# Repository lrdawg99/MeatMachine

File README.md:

# MeatMachine
Internet connected electric meat smoker

BOM
=======
- 1 Thermocouple https://www.sparkfun.com/products/251
- 1 Therm. amp. https://www.adafruit.com/products/1727
- 1 LED https://www.sparkfun.com/products/10866
- 2 screw terminals http://www.digikey.com/scripts/DkSearch/dksus.dll?Detail&itemSeq=171773812&uq=635679932379437882
- 1 SSR http://www.digikey.com/scripts/DkSearch/dksus.dll?Detail&itemSeq=171772005&uq=635680054867597191
- Female headers
- 1 BSS138 http://www.mouser.com/ProductDetail/Fairchild-Semiconductor/BSS138/?qs=HK%252beIG1iaahCeqBvjB4arg%3D%3D
- Assorted 0805 resistors

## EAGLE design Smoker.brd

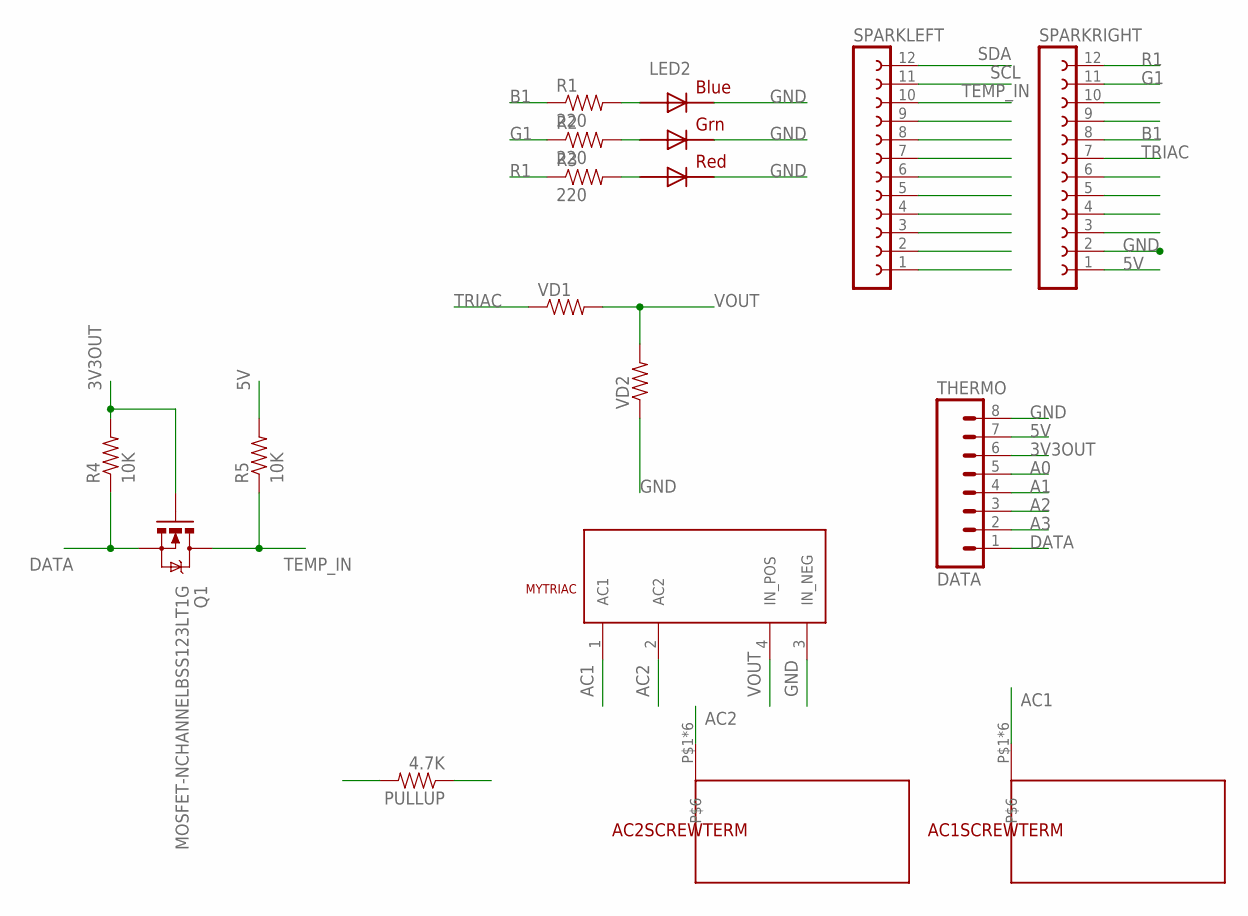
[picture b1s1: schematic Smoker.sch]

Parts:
AC1SCREWTERM, AC2SCREWTERM: SCREW_TERM_8197
LED2: RGBLED5050
MYTRIAC: S116S01
PULLUP: 4.7K; 0805
Q1: MOSFET-NCHANNELBSS123LT1G; SOT23
R1, R2, R3: 220; 0805
R4, R5: 10K; 0805
SPARKLEFT: FE12-1; FE12
SPARKRIGHT: FE12-1; FE12
THERMO: DATA; 1X08
VD1, VD2: RESISTOR0805-RES; 0805

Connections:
3V3OUT: PULLUP.1, Q1.1 (G), R4.2, THERMO.6
5V: R5.2, SPARKRIGHT.1, THERMO.7
A0: THERMO.5
A1: THERMO.4
A2: THERMO.3
A3: THERMO.2
AC1: AC1SCREWTERM.P$1, AC1SCREWTERM.P$2, AC1SCREWTERM.P$3, AC1SCREWTERM.P$4, AC1SCREWTERM.P$5, AC1SCREWTERM.P$6, MYTRIAC.1 (AC1)
AC2: AC2SCREWTERM.P$1, AC2SCREWTERM.P$2, AC2SCREWTERM.P$3, AC2SCREWTERM.P$4, AC2SCREWTERM.P$5, AC2SCREWTERM.P$6, MYTRIAC.2 (AC2)
B1: R1.1, SPARKRIGHT.8
DATA: PULLUP.2, Q1.2 (S), R4.1, THERMO.1
G1: R2.1, SPARKRIGHT.11
GND: LED2.4 (BLUE_C), LED2.5 (RED_C), LED2.6 (GREEN_C), MYTRIAC.3 (IN_NEG), SPARKRIGHT.2, THERMO.8, VD2.1
unnamed: LED2.3 (BLUE_A), R1.2
unnamed: LED2.1 (GREEN_A), R2.2
unnamed: LED2.2 (RED_A), R3.2
R1: R3.1, SPARKRIGHT.12
SCL: SPARKLEFT.11
SDA: SPARKLEFT.12
TEMP_IN: Q1.3 (D), R5.1, SPARKLEFT.10
TRIAC: SPARKRIGHT.7, VD1.1
VOUT: MYTRIAC.4 (IN_POS), VD1.2, VD2.2

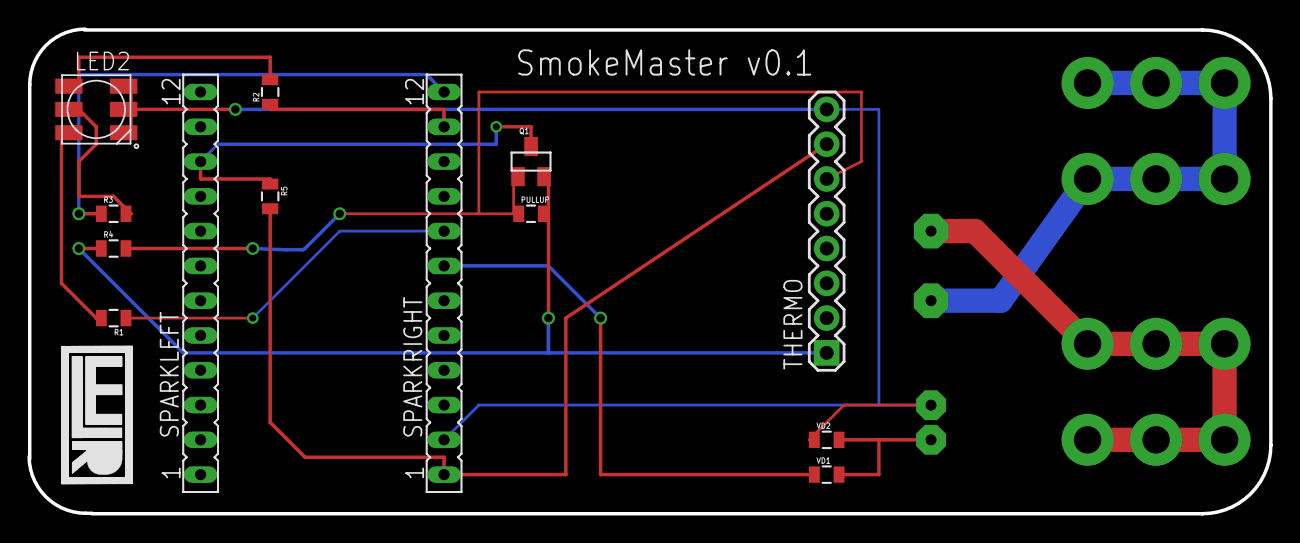
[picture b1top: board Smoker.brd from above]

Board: 2 copper layers, 90.7 x 35.4 mm, 16 parts (0 on the bottom side), 15 nets.

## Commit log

2015-05-24 Files
2015-05-24 Update README.md
    updated readme with bom
2015-05-24 Update README.md
    markdown fix

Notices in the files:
parts and their libraries:
SparkFun-Resistors: Licensing: Creative Commons ShareAlike 4.0 International - https://creativecommons.org/licenses/by-sa/4.0
